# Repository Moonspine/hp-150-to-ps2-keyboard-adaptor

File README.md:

# hp-150-to-ps2-keyboard-adaptor
This project contains code and design files to build an adaptor that lets an HP-150 computer talk to a PS/2 keyboard.

## Purpose
I recently repaired and restored an old HP-150 computer from the brink of death.
After I finally got the video board working again, I realized that I couldn't do anything without a keyboard.
However, these keyboards are not a standard type (HP decided not to go with IBM PC compatibility on this one).
Checking the 'Net, I noticed that these keyboards sold for outrageous prices.
"Why not just adapt a PS/2 keyboard?" I wondered. So I dug into the schematics and wrote an Arduino program to read a PS/2 keyboard and pretend to be an HP-150 keyboard.

## Which computers can use this?
The [HP-150](http://hpmuseum.net/display_item.php?hw=43). It's a nifty little touchscreen computer from 1983.
I'm uncertain if this will work with of HP's other oddball nonstandard computers (possibly other computers in their 100 series).
So... it's a pretty niche project.
If you do use this with another computer, let me know, and I'll add it to this list.

## How do I make one?
First, you'll want to make a PCB. This can be done cheaply via your favorite Chinese PCB manufacturer (as of this writing, mine is [JLCPCB](https://jlcpcb.com/), #NotSponsored).
The Gerber files are already premade for you (in the [Gerber](Gerber) folder in this repository). But if you want to modify the board before manufacture, the design files are in the [Board](Board) folder (I used [KiCad 6](https://www.kicad.org/download/) to create them).

Second, you'll need to assemble the board. I recommend checking the schematics in [Board](Board) to see the exact part values I used. You can get some RJ-12 cables and connectors and PS/2 connectors from Amazon or eBay as well.

Third, you'll need to burn the program to an ATMEGA328p. There are many ways to do this, but I used an ICSP to program via the ICSP header on the board using Arduino 1.8.12

There are a couple of optional steps, too!

First, you can print an enclosure to hold the PCB and protect it from dust and your own clumsiness. I definitely did this.
The files are in [3D Printing](3D Printing), and if you happen to have a Photon Mono X 6K, you can use those *.pwmb files directly. Otherwise, you'll need to use the STL files and do what you do best.
The screws that hold the case together are meant to be M3 screws with brass inserts in the bottom of the case, but you can modify this design to fit whatever you want to do.

The second optional step is to print the [keyboard decals](Keyboard Decals.xcf) and affix them to the specialty keys on your PS/2 keyboard (see the [keymap](Keymap.txt) for details on how I set these up by default).
You can always remap these keys by modifying the program (specifically [ps2_to_hp_map.h](Code/PS2_Keyboard_Adaptor/ps2_to_hp_map.h))

## License
This entire project is licensed under the MIT license. Feel free to do whatever with it! If it helps even one person, then it was a good idea for me to upload it to Github.

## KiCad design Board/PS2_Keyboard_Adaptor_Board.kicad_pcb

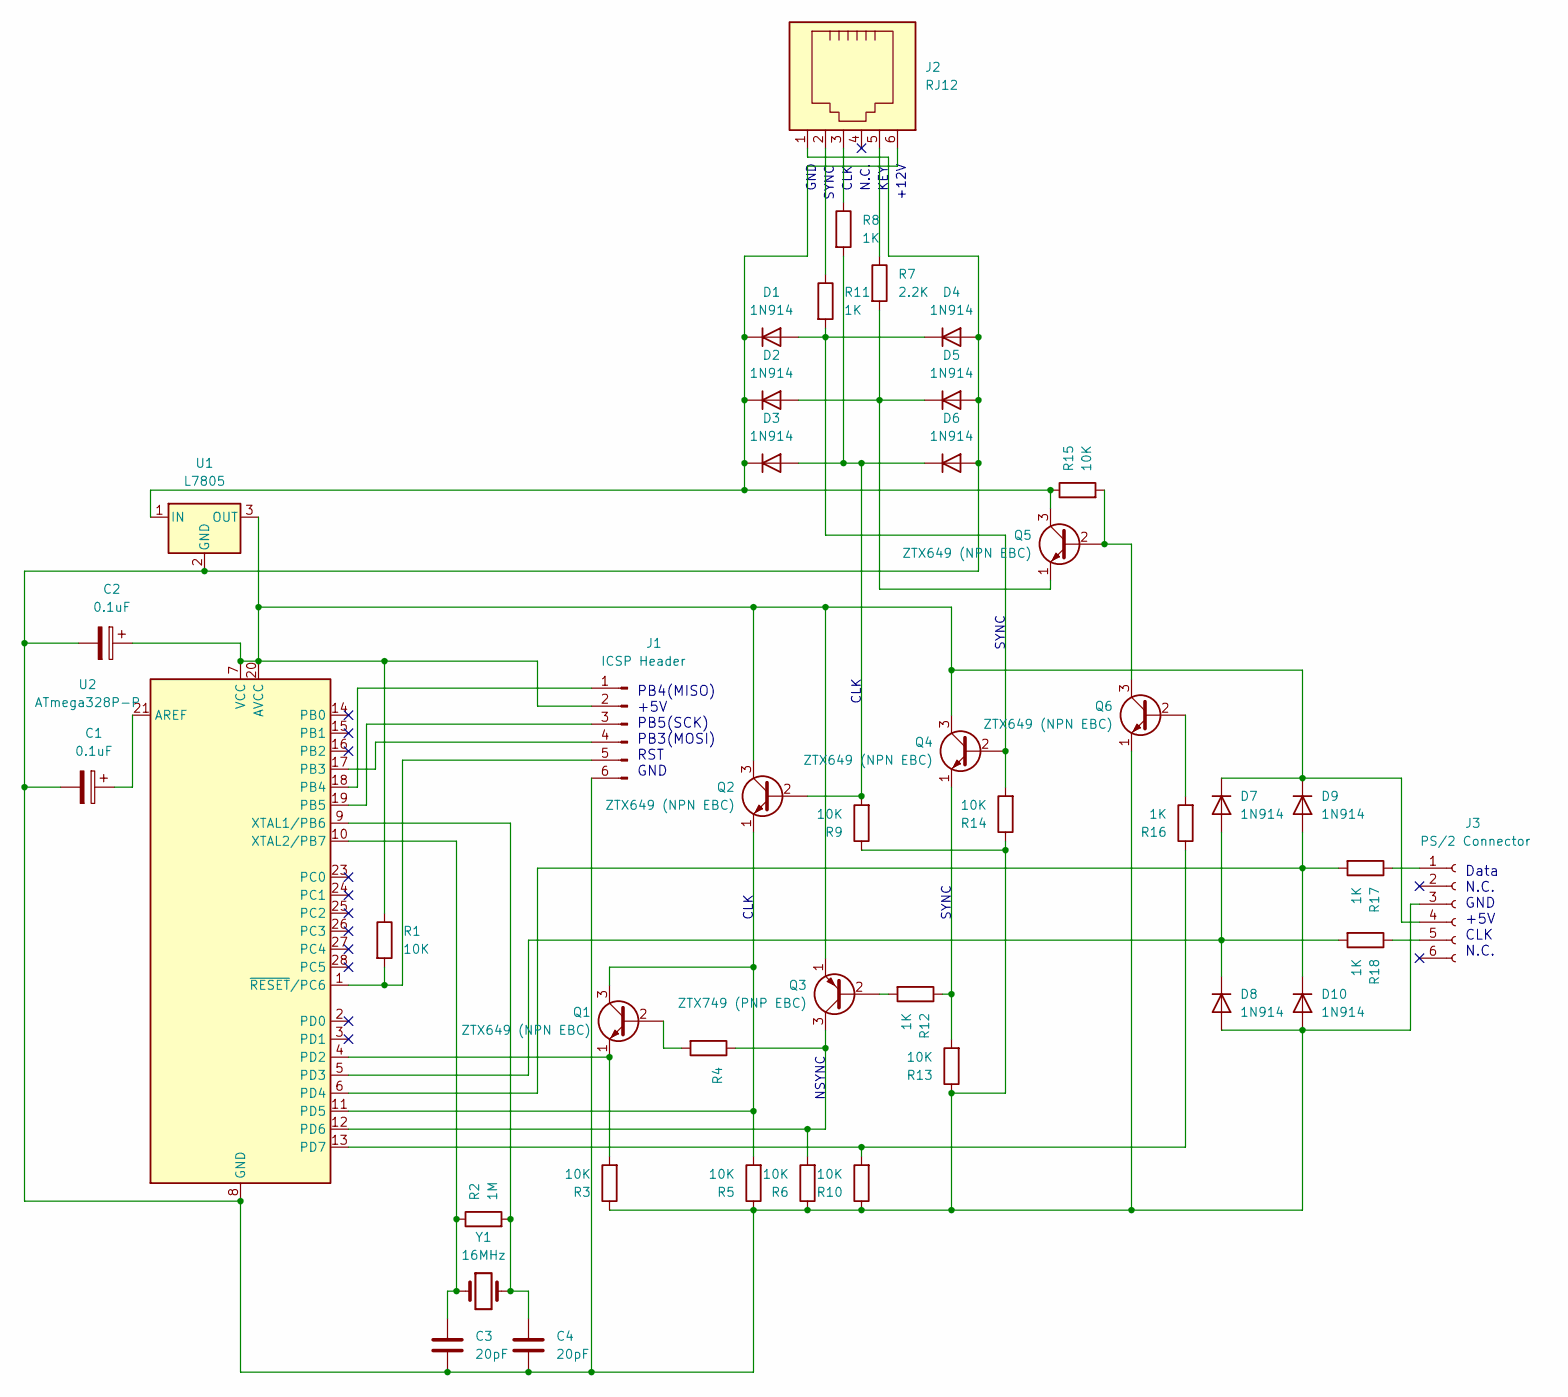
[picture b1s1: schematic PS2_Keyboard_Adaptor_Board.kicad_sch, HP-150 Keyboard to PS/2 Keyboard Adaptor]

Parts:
C1, C2: 0.1uF; CP_Radial_Tantal_D5.0mm_P2.50mm
C3, C4: 20pF; C_Disc_D5.0mm_W2.5mm_P2.50mm
D1, D2, D3, D4, D5, D6, D7, D8, D9, D10: 1N914; D_DO-34_SOD68_P7.62mm_Horizontal
J1: ICSP Header; PinHeader_2x03_P2.54mm_Vertical
J2: RJ12; RJ12_Amphenol_54601
J3: PS/2 Connector; PS2_Connector_F
Q1, Q2, Q4, Q5, Q6: ZTX649 (NPN EBC); TO-92L_Inline
Q3: ZTX749 (PNP EBC); TO-92_Inline
R1, R3, R5, R6, R9, R10, R13, R14, R15: 10K; R_Axial_DIN0207_L6.3mm_D2.5mm_P10.16mm_Horizontal
R2: 1M; R_Axial_DIN0207_L6.3mm_D2.5mm_P10.16mm_Horizontal
R4: R_Axial_DIN0207_L6.3mm_D2.5mm_P10.16mm_Horizontal
R7: 2.2K; R_Axial_DIN0207_L6.3mm_D2.5mm_P10.16mm_Horizontal
R8, R11, R12, R16, R17, R18: 1K; R_Axial_DIN0207_L6.3mm_D2.5mm_P10.16mm_Horizontal
U1: L7805; TO-220-3_Vertical
U2: ATmega328P-P; DIP-28_W7.62mm
Y1: 16MHz; Crystal_HC49-U_Vertical

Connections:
unnamed: C1.1, U2.21 (AREF)
unnamed: C1.2, C2.2, C3.2, C4.2, D4.2 (A), D5.2 (A), D6.2 (A), D8.2 (A), D10.2 (A), J1.6, J2.1, J3.3, Q6.1 (E), R3.1, R5.1, R6.1, R9.1, R10.1, R13.1, R14.1, U1.2 (GND), U2.8 (GND), U2.22 (GND)
unnamed: C2.1, D7.1 (K), D9.1 (K), J1.2, J3.4, Q2.3 (C), Q3.1 (E), Q4.3 (C), R1.1, U1.3 (OUT), U2.7 (VCC), U2.20 (AVCC)
unnamed: C3.1, R2.1, U2.10 (XTAL2/PB7), Y1.1
unnamed: C4.1, R2.2, U2.9 (XTAL1/PB6), Y1.2
unnamed: D1.1 (K), D2.1 (K), D3.1 (K), J2.6, Q5.3 (C), R15.1, U1.1 (IN)
unnamed: D1.2 (A), D4.1 (K), Q4.2 (B), R11.2, R14.2
unnamed: D2.2 (A), D5.1 (K), Q5.1 (E), R7.2
unnamed: D3.2 (A), D6.1 (K), Q2.2 (B), R8.2, R9.2
unnamed: D7.2 (A), D8.1 (K), R18.2, U2.5 (PD3)
unnamed: D9.2 (A), D10.1 (K), R17.2, U2.6 (PD4)
unnamed: J1.1, U2.18 (PB4)
unnamed: J1.3, U2.19 (PB5)
unnamed: J1.4, U2.17 (PB3)
unnamed: J1.5, R1.2, U2.1 (~RESET/PC6)
unnamed: J2.2, R11.1
unnamed: J2.3, R8.1
unnamed: J2.5, R7.1
unnamed: J3.1, R17.1
unnamed: J3.5, R18.1
unnamed: Q1.1 (E), R3.2, U2.4 (PD2)
unnamed: Q1.2 (B), R4.2
unnamed: Q1.3 (C), Q2.1 (E), R5.2, U2.11 (PD5)
unnamed: Q3.2 (B), R12.2
unnamed: Q3.3 (C), R4.1, R6.2, U2.12 (PD6)
unnamed: Q4.1 (E), R12.1, R13.2
unnamed: Q5.2 (B), Q6.3 (C), R15.2
unnamed: Q6.2 (B), R16.2
unnamed: R10.2, R16.1, U2.13 (PD7)

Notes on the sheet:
GND
CLK
NSYNC
SYNC
KEY
Data N.C. GND +5V CLK N.C.
PB4(MISO) +5V PB5(SCK) PB3(MOSI) RST GND
N.C.
+12V

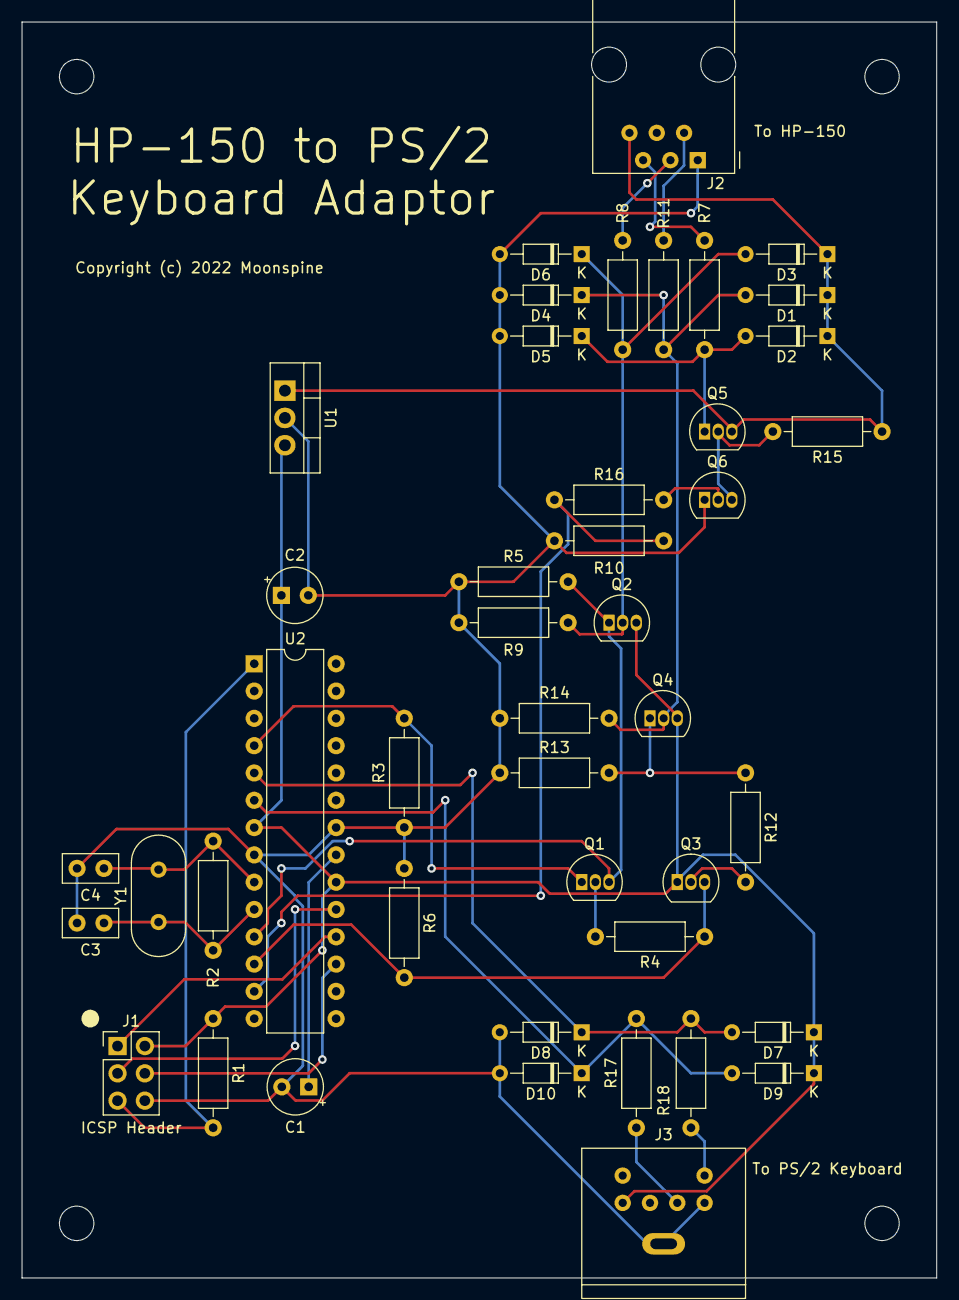
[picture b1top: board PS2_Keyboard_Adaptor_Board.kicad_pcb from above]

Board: 2 copper layers, 85.1 x 116.8 mm, 44 parts (0 on the bottom side), 29 nets.

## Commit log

2022-07-08 Added readme
2022-07-08 Missing period

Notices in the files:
Board/PS2_Keyboard_Adaptor_Board.kicad_pcb:
Copyright (c) 2022 Moonspine
